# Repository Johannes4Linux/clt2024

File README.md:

# CLT2024 Linux Treiber Workshop

Am 16.03.2024 durfte ich einen Linux Treiber Workshop auf den [Chemnitzer Linuxtagen](https://chemnitzer.linux-tage.de/2024/de) halten. In diesem Repo sind die Code Beispiele sowie meine Präsentation zu finden.

## Inhalt

- cdev: Beispiel für die Verwendung eines Character Devices
- gpio: Beispiel für die Nutzung von GPIOs in einem Linux Treiber
- hello: Hello World Linux Kernel Modul
- segment: Treiber für eine 7 Segmentanzeige und einem Taster
- pcb: Schaltplan und Layout für die verwendete Adapterplatine
- treiber_workshop.pdf: PDF mit Folien für den Workshop
- gpio.c: Programm zur Ansteuerung eines GPIO Pins im Userspace 

## Video

Ich habe einen Übungslauf für den Workshop aufgenommen und auf [YouTube](https://youtu.be/xk0xdN2SzV0) veröffentlicht. Ist allerdings englisch

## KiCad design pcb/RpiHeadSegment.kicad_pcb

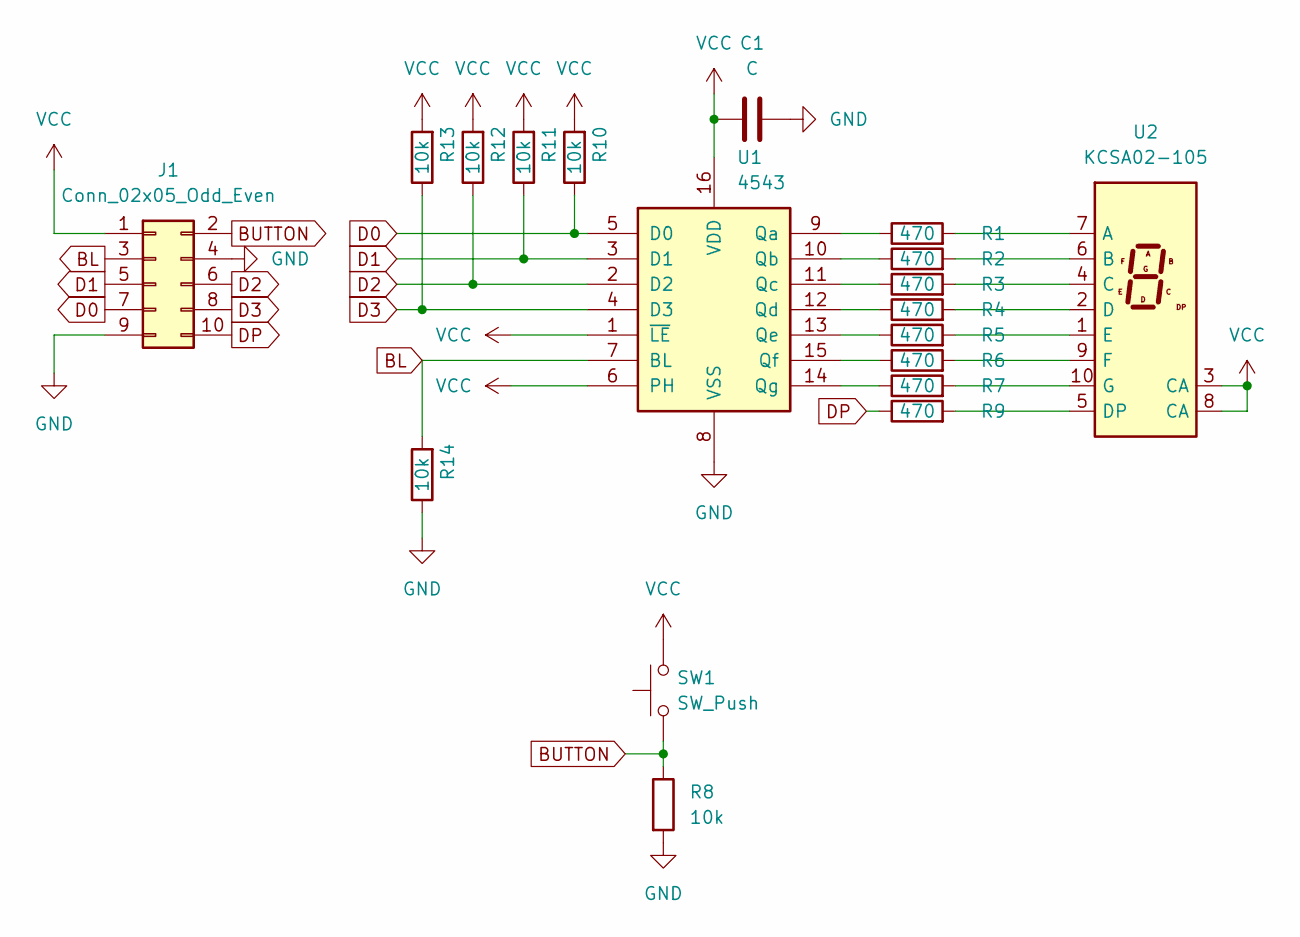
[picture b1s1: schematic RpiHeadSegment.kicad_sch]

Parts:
C1: C; C_0402_1005Metric_Pad0.74x0.62mm_HandSolder
J1: Conn_02x05_Odd_Even; PinSocket_2x05_P2.54mm_Vertical
R1, R2, R3, R4, R5, R6, R7: 470; R_0402_1005Metric_Pad0.72x0.64mm_HandSolder
R8, R10, R11, R12, R13, R14: 10k; R_0402_1005Metric_Pad0.72x0.64mm_HandSolder
R9: 470; C_0402_1005Metric_Pad0.74x0.62mm_HandSolder
SW1: SW_Push; SW_SPST_FSMSM
U1: 4543; SOIC-16_3.9x9.9mm_P1.27mm
U2: KCSA02-105; KCSC02-105

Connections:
BL: J1.3, R14.2, U1.7 (BL)
BUTTON: J1.2, R8.1, SW1.1
D0: J1.7, R10.1, U1.5 (D0)
D1: J1.5, R11.1, U1.3 (D1)
D2: J1.6, R12.1, U1.2 (D2)
D3: J1.8, R13.1, U1.4 (D3)
DP: J1.10, R9.1
GND: C1.2, J1.4, J1.9, R8.2, R14.1, U1.8 (VSS)
unnamed: R1.1, U1.9 (Qa)
unnamed: R2.1, U1.10 (Qb)
unnamed: R3.1, U1.11 (Qc)
unnamed: R4.1, U1.12 (Qd)
unnamed: R5.1, U1.13 (Qe)
unnamed: R6.1, U1.15 (Qf)
unnamed: R7.1, U1.14 (Qg)
unnamed: R1.2, U2.7 (A)
unnamed: R2.2, U2.6 (B)
unnamed: R3.2, U2.4 (C)
unnamed: R4.2, U2.2 (D)
unnamed: R9.2, U2.5 (DP)
unnamed: R5.2, U2.1 (E)
unnamed: R6.2, U2.9 (F)
unnamed: R7.2, U2.10 (G)
VCC: C1.1, J1.1, R10.2, R11.2, R12.2, R13.2, SW1.2, U1.1 (~LE), U1.6 (PH), U1.16 (VDD), U2.3 (CA), U2.8 (CA)

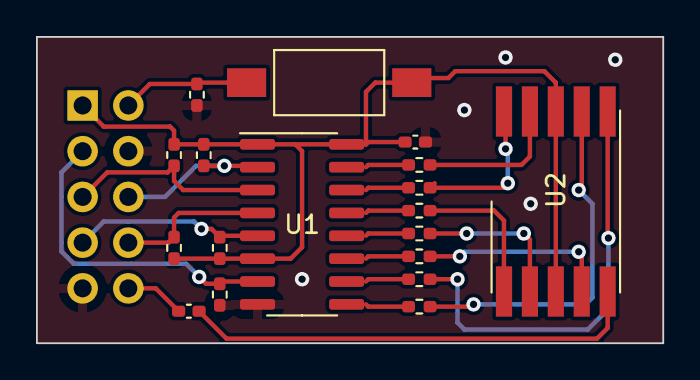
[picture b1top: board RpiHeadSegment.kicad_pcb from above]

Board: 2 copper layers, 34.8 x 17.0 mm, 19 parts (1 on the bottom side), 24 nets.

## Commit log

2024-03-16 Erste Sourcen hinzugefügt
2024-03-23 KiCad Projekt für Adapterplatine hinzugefügt
2024-03-23 README update
